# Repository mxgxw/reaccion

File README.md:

Red de Acción Comunitaria (Reaccion.net)
========================================

"Reaccion.net es una Red de Acción Comunitaria que hace uso de un
dispositivo electrónico que facilita la comunicación y coordinación
de comunidades en caso de siniestros, canalizando eficazmente la
información de alerta temprana y necesidades básicas durante
y después de una emergencia..."

El dispositivo consiste en un módulo de transmisión de datos
inalámbrico diseñado específicamente para enviar mensajes
pre-acordados en la forma de mensajes cortos tipo "semáforo"
indicando distintos niveles de alerta o impácto en una comunidad.
Los dispositivos almacenan y actualizan la información entre si al
estilo de una red P2P de tal manera que la información se guarda
de manera distribuida en toda la red.

En este proyecto de GitHub encontrarás las notas de diseño,
diagramas eléctricos, diseños de las tabletas de circuito impreso,
hojas técnicas y el sofware necesario para controlar el kit Reaccion.net.

Puedes apoyar este proyecto haciendo un "Fork" del mismo, agregando
mejoras al diseño y/o funcionamiento e incorporándolas de nuevo a
través de un "pull request".

Ayúdanos a materializar esta idea a través de SocialLab iniciado
sesión con Faceebok y haciendo click a "Vota por esta idea":

http://www.socialab.com/ideas/ver/15704

Para más información contactanos a través de nuestro
email: info _arroba_ reaccion *punto* net.

Últimas adiciones
=================

+Agregadas las hojas técnicas de los componentes bajo extra/Datasheets.

Costo/Lista de Materiales
=========================

Encuentra la lista de materiales en el archivo bom.csv

Pre-requisitos/Requerimientos
=============================

Pendiente diseño del módulo de cargador/regulador de voltaje LiPO.

Construcción y uso
==================

// TO DO

Carpetas
========

```
raíz
 |--dsn: Archivos de diseño
 |   |--main: Esquemáticos y diagrama de PCB para Eagle.
 |   |--auxiliar: Esquemático y diagrama de PCB en formato PDF imprimible.
 |--doc: Archivos de documentación para construcción y uso.
 |--src: Código fuente del software de control (Arduino).
 |--extra: Anexos
     |--Datasheets: Hojas técnicas de los componentes utilizados.
     |--Gráficos: Renders y bocetos del diseño.
     |--sketchs: Esquemas a mano rápidamente.
```

Excepción de responsabilidades
==============================

> El presente proyecto se comparte "tal cual" con el único objetivo de que sea útil.
El/los creadores del presente hardware y su software asociado no pueden garantizar su
correcto funcionamiento bajo ninguna circunstancia. El/Los autor/es de este proyecto
no podrá/n hacerse responsable/s de cualquier pérdida de carácter material, personal o
económico a su persona o terceros derivados de la utilización del mismo. Este diseño
utiliza componentes emisores de radiofrecuencia que podrían requerir algún tipo de
licenciamiento o pruebas de emisiones antes de su puesta en funcionamiento, asegurate
de estar al tanto de las regulaciones locales respecto al tema.

Licenciamiento
==============
El código fuente del software utilizado en este proyecto está protegido bajo la
licencia GNU/GPL v2.0.

Los archivos de diseño principales y auxiliares están liberados bajo la licencia
CC-BY-SA 3.0 ( https://creativecommons.org/licenses/by-sa/3.0/ ).

> La plantilla de este README.md ha sido desarrollada por la comunidad openhardware.sv
con el objetivo de facilitar la documentación de proyectos. Esta plantilla está protegida
bajo la licencia CC BY, puedes modificarla y redistribuirla manteniendo esta nota de
atribución del autor.

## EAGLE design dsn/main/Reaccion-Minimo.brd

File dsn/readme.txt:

Archivos de diseño
==================

Encuentra en esta carpeta los archivos de diagramas eléctricos para el
armado del módulo de tranmisión de datos.

Archivos de diseño principal:

* main\Enlaza.sch : Archivo fuente del diagráma eléctrico para Eagle.
* main\Enlaza.brd : Archivo fuente de la tableta impresa para Eagle.

Archivos de diseño auxiliar:
* auxiliar\Enlaza.pdf : PDF para impresión del diagrama eléctrico.

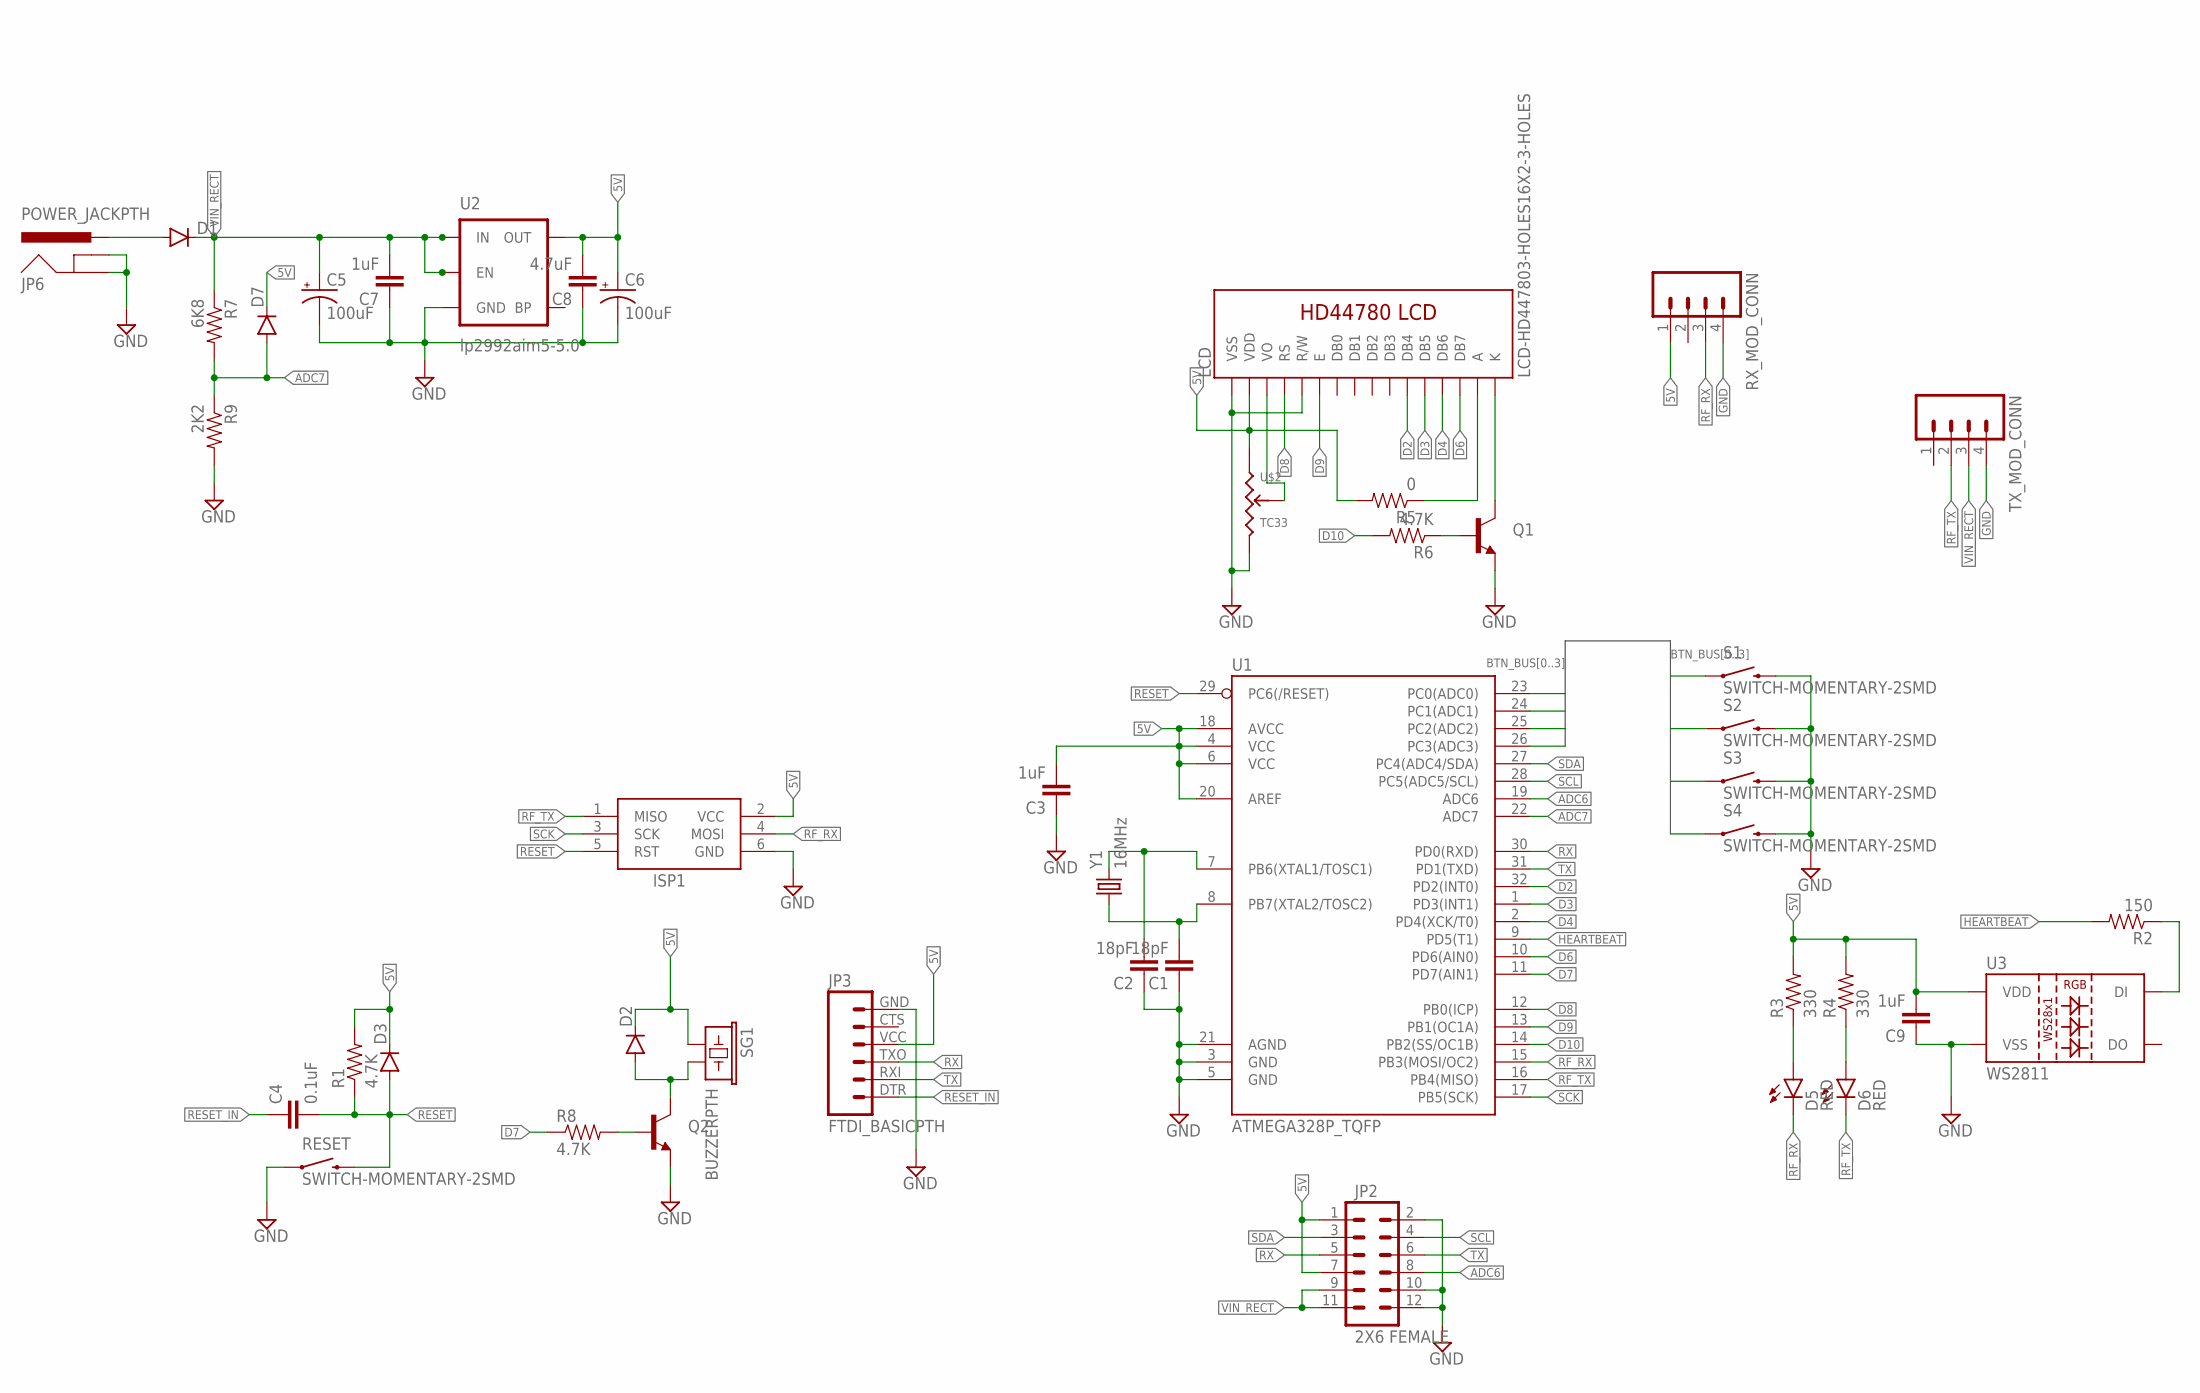
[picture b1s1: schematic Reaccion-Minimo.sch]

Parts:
C1, C2: 18pF; 0805
C3, C7, C9: 1uF; 0805
C4: 0.1uF; 0805
C5: 100uF; C/6032-28R
C6: 100uF; T/3528-12R
C8: 4.7uF; 0805
D1: DIODESMB; SMB-DIODE
D2, D3, D7: DIODESOD123; SOD-123
D5, D6: RED; LED-1206
ISP1: AVRISP-6; AVRISP
JP2: 2X6 FEMALE; 2X6
JP3: FTDI_BASICPTH; FTDI_BASIC
JP6: POWER_JACKPTH; POWER_JACK_PTH
LCD: LCD-HD447803-HOLES16X2-3-HOLES; LCD-16X2-3HOLES
Q1, Q2: TRANSISTOR_NPNSOT23-3; SOT23-3
R1, R6, R8: 4.7K; 0805
R2: 150; 0805
R3, R4: 330; 0805
R5: 0; 0805
R7: 6K8; 0805
R9: 2K2; 0805
RESET: SWITCH-MOMENTARY-2SMD; TACTILE-SWITCH-SMD
RX_MOD_CONN: M04PTH; 1X04
S1, S2, S3, S4: SWITCH-MOMENTARY-2SMD; TACTILE-SWITCH-SMD
SG1: BUZZERPTH; BUZZER-12MM
TX_MOD_CONN: M04PTH; 1X04
U1: ATMEGA328P_TQFP; TQFP32-08
U2: lp2992aim5-5.0; SOT23-5
U3: WS2811; LED-TRICOLOR-5050-IC
U$2: TC33
Y1: 16MHz; CRYSTAL-SMD-5X3

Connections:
5V: C3.2, C6.+, C8.2, C9.2, D2.C, D3.C, D7.C, ISP1.2 (VCC), JP2.1, JP2.7, JP3.VCC (4), LCD.2 (VDD), R1.2, R3.2, R4.2, R5.2, RX_MOD_CONN.1, SG1.+ (1), U1.4 (VCC), U1.6 (VCC), U1.18 (AVCC), U1.20 (AREF), U2.5 (OUT), U3.3 (VDD), U3.5 (VDD), U$2.1
ADC6: JP2.8, U1.19 (ADC6)
ADC7: D7.A, R7.2, R9.1, U1.22 (ADC7)
BTN_BUS0: S1.1, U1.23 (PC0(ADC0))
BTN_BUS1: S2.1, U1.24 (PC1(ADC1))
BTN_BUS2: S3.1, U1.25 (PC2(ADC2))
BTN_BUS3: S4.1, U1.26 (PC3(ADC3))
D2: LCD.11 (DB4), U1.32 (PD2(INT0))
D3: LCD.12 (DB5), U1.1 (PD3(INT1))
D4: LCD.13 (DB6), U1.2 (PD4(XCK/T0))
D6: LCD.14 (DB7), U1.10 (PD6(AIN0))
D7: R8.1, U1.11 (PD7(AIN1))
D8: LCD.4 (RS), U1.12 (PB0(ICP))
D9: LCD.6 (E), U1.13 (PB1(OC1A))
D10: R6.2, U1.14 (PB2(SS/OC1B))
GND: C1.1, C2.1, C3.1, C5.-, C6.-, C7.1, C8.1, C9.1, ISP1.6 (GND), JP2.2, JP2.10, JP2.12, JP3.GND (6), JP6.GND, JP6.GNDBREAK, LCD.1 (VSS), LCD.5 (R/W), Q1.2 (E), Q2.2 (E), R9.2, RESET.1, RX_MOD_CONN.4, S1.3 (2), S2.3 (2), S3.3 (2), S4.3 (2), TX_MOD_CONN.4, U1.3 (GND), U1.5 (GND), U1.21 (AGND), U2.2 (GND), U3.6 (VSS), U$2.3
HEARTBEAT: R2.2, U1.9 (PD5(T1))
unnamed: C2.2, U1.7 (PB6(XTAL1/TOSC1)), Y1.3 (2)
unnamed: C1.2, U1.8 (PB7(XTAL2/TOSC2)), Y1.1
unnamed: R2.1, U3.2 (DI)
unnamed: D5.A, R3.1
unnamed: D6.A, R4.1
unnamed: LCD.15 (A), R5.1
unnamed: LCD.3 (VO), U$2.2
unnamed: LCD.16 (K), Q1.3 (C)
unnamed: Q1.1 (B), R6.1
unnamed: D2.A, Q2.3 (C), SG1.- (2)
unnamed: Q2.1 (B), R8.2
RESET: C4.2, D3.A, ISP1.5 (RST), R1.1, RESET.3 (2), U1.29 (PC6(/RESET))
RESET_IN: C4.1, JP3.DTR (1)
RF_RX: D5.C, ISP1.4 (MOSI), RX_MOD_CONN.3, U1.15 (PB3(MOSI/OC2))
RF_TX: D6.C, ISP1.1 (MISO), TX_MOD_CONN.2, U1.16 (PB4(MISO))
RX: JP2.5, JP3.TXO (3), U1.30 (PD0(RXD))
SCK: ISP1.3 (SCK), U1.17 (PB5(SCK))
SCL: JP2.4, U1.28 (PC5(ADC5/SCL))
SDA: JP2.3, U1.27 (PC4(ADC4/SDA))
TX: JP2.6, JP3.RXI (2), U1.31 (PD1(TXD))
VIN: D1.A, JP6.PWR
VIN_RECT: C5.+, C7.2, D1.C, JP2.9, JP2.11, R7.1, TX_MOD_CONN.3, U2.1 (IN), U2.3 (EN)

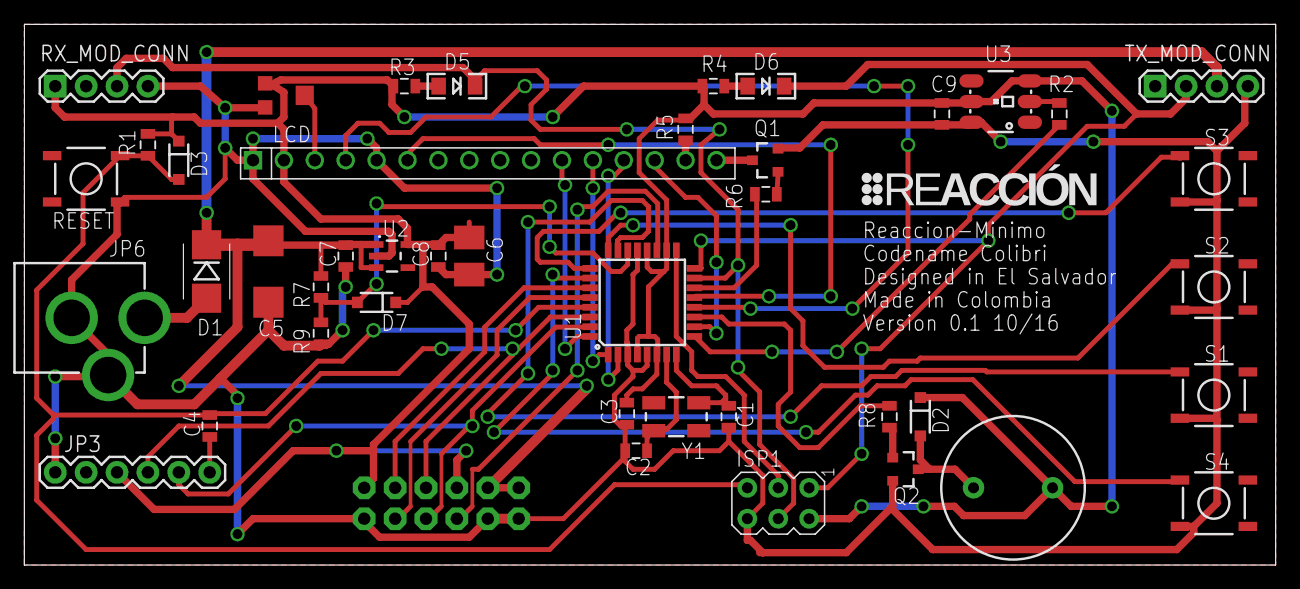
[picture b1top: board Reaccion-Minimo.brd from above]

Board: 2 copper layers, 102.9 x 44.5 mm, 44 parts (1 on the bottom side), 39 nets.

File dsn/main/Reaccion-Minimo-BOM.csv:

"Qty";"Value";"Device";"Package";"Parts";"Description";"PROD_ID";"VALUE";
"1";"";"DIODESMB";"SMB-DIODE";"D1";"Diode";"DIO-09646";"";
"3";"";"DIODESOD123";"SOD-123";"D2, D3, D7";"Diode";"";"";
"2";"";"M04PTH";"1X04";"RX_MOD_CONN, TX_MOD_CONN";"Header 4";"";"";
"2";"";"TRANSISTOR_NPNSOT23-3";"SOT23-3";"Q1, Q2";"Generic NPN BJT";"TRANS-08049";"";
"1";"0";"RESISTOR0805-RES";"0805";"R5";"Resistor";"";"";
"1";"0.1uF";"CAP0805";"0805";"C4";"Capacitor";"";"";
"1";"100uF";"CPOL-USB/3528-21R";"T/3528-12R";"C6";"POLARIZED CAPACITOR, American symbol";"";"";
"1";"100uF";"CPOL-USC/6032-28R";"C/6032-28R";"C5";"POLARIZED CAPACITOR, American symbol";"";"";
"1";"10K";"RESISTOR0805-RES";"0805";"R1";"Resistor";"";"";
"1";"150";"RESISTOR0805-RES";"0805";"R2";"Resistor";"";"";
"1";"16MHz";"CRYSTAL5X3";"CRYSTAL-SMD-5X3";"Y1";"Various standard crystals. Proven footprints.";"XTAL-08218";"";
"2";"18pF";"CAP0805";"0805";"C1, C2";"Capacitor";"";"";
"3";"1uF";"CAP0805";"0805";"C3, C7, C9";"Capacitor";"";"";
"1";"2K2";"RESISTOR0805-RES";"0805";"R9";"Resistor";"";"";
"1";"2X6 FEMALE";"M06X2PTH_FEMALE";"2X6";"JP2";"";"CONN-12423";"2X6 FEMALE";
"2";"330";"RESISTOR0805-RES";"0805";"R3, R4";"Resistor";"";"";
"2";"4.7K";"RESISTOR0805-RES";"0805";"R6, R8";"Resistor";"";"";
"1";"4.7uF";"CAP0805";"0805";"C8";"Capacitor";"";"";
"1";"6K8";"RESISTOR0805-RES";"0805";"R7";"Resistor";"";"";
"1";"ATMEGA328P_TQFP";"ATMEGA328P_TQFP";"TQFP32-08";"U1";"";"IC-09069";"ATMEGA328P_TQFP";
"1";"AVRISP-6";"AVRISP-6";"AVRISP";"ISP1";"AVR ISP HEADER";"";"";
"1";"BUZZERPTH";"BUZZERPTH";"BUZZER-12MM";"SG1";"Buzzer 12mm";"";"";
"1";"FTDI_BASICPTH";"FTDI_BASICPTH";"FTDI_BASIC";"JP3";"FTDI Basic header with labels";"";"";
"1";"LCD-HD447803-HOLES16X2-3-HOLES";"LCD-HD447803-HOLES16X2-3-HOLES";"LCD-16X2-3HOLES";"LCD";"";"";"";
"1";"MIC5219 5V";"V_REG_MIC52195V";"SOT23-5";"U2";"V_REG MIC5219";"VREG-10107";"MIC5219 5V";
"1";"POWER_JACKPTH";"POWER_JACKPTH";"POWER_JACK_PTH";"JP6";"Power Jack";"CONN-08197";"";
"2";"RED";"LED-RED1206";"LED-1206";"D5, D6";"Assorted Red LEDs";"DIO-09912";"RED";
"5";"SWITCH-MOMENTARY-2SMD";"SWITCH-MOMENTARY-2SMD";"TACTILE-SWITCH-SMD";"RESET, S1, S2, S3, S4";"Various NO switches- pushbuttons, reed, etc";"SWCH-08247";"";
"1";"TC33";"TC33";"TC33";"U$2";"";"";"";
"1";"WS2811";"LED-TRICOLOR-5050-ICWS2811";"LED-TRICOLOR-5050-IC";"U3";"WS2812 RGB LED w/ WS2811 driver";"DIO-11598";"WS2811";

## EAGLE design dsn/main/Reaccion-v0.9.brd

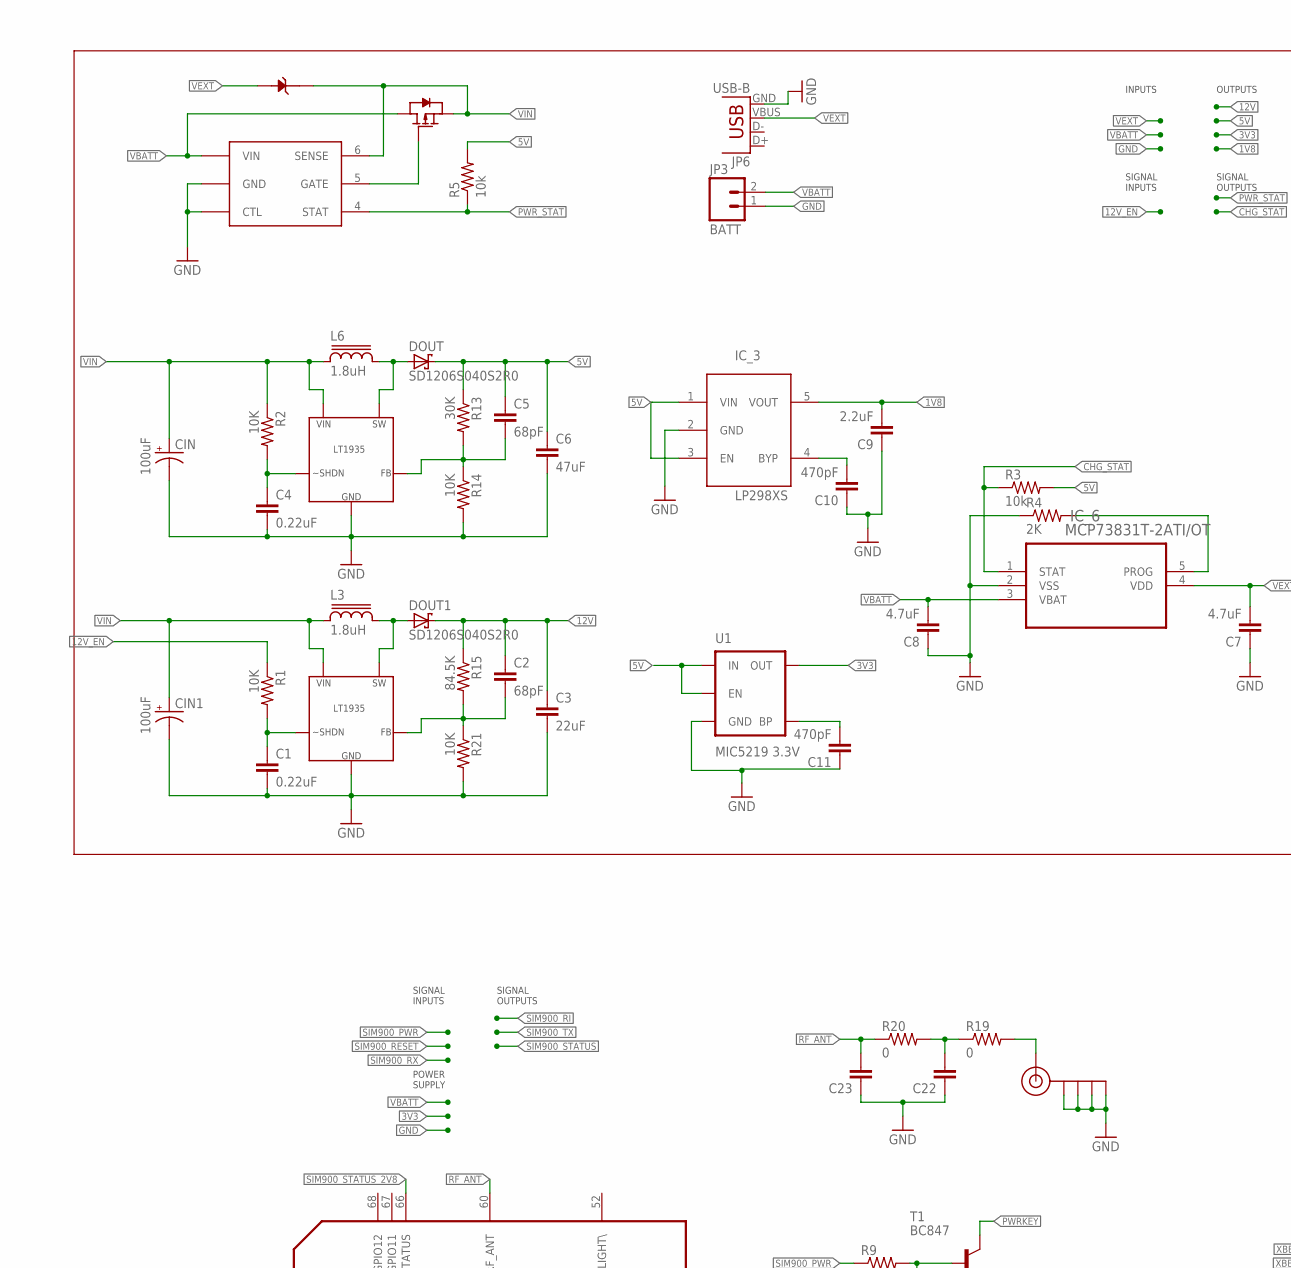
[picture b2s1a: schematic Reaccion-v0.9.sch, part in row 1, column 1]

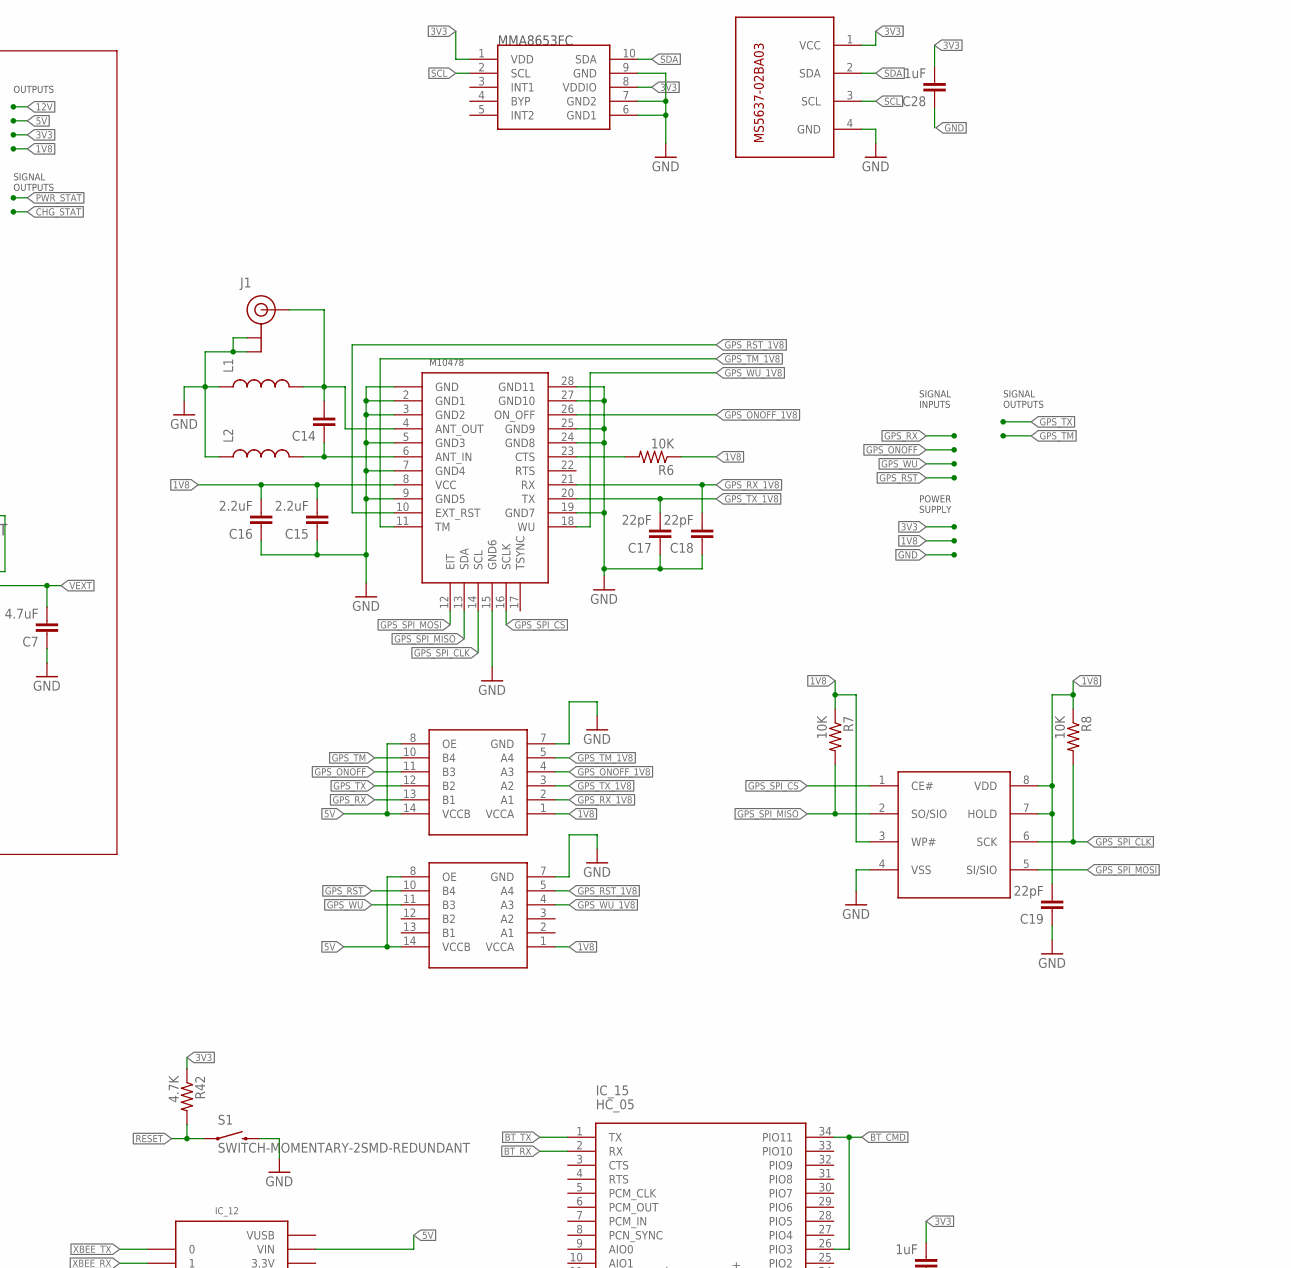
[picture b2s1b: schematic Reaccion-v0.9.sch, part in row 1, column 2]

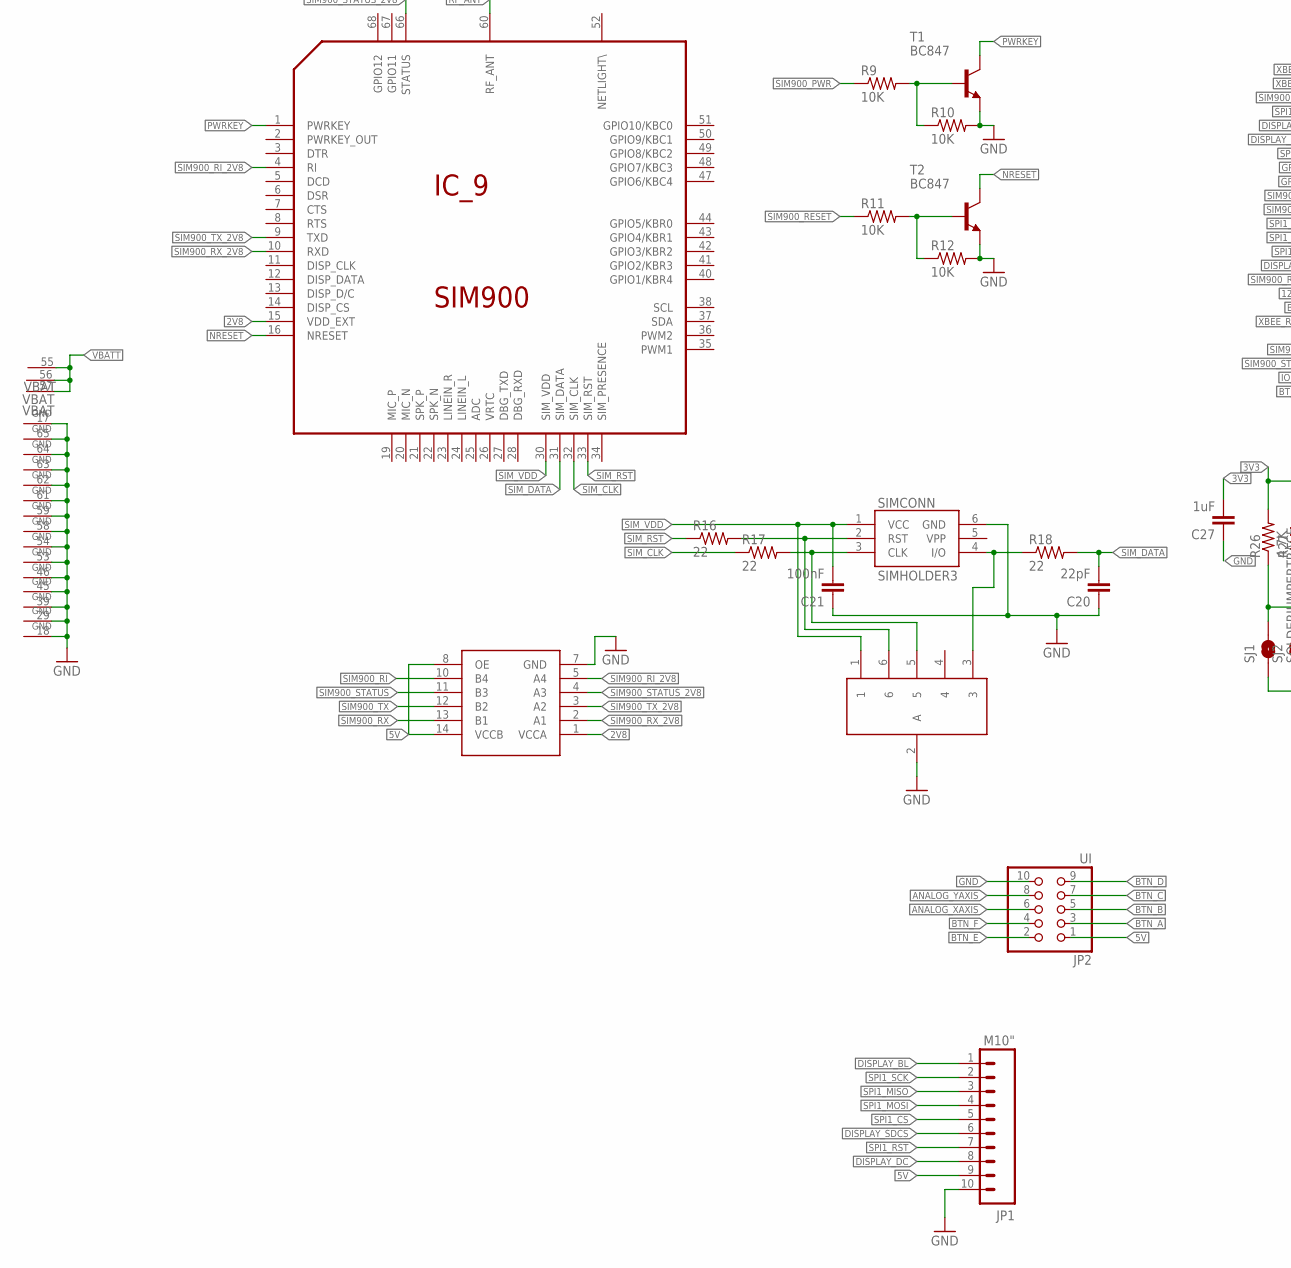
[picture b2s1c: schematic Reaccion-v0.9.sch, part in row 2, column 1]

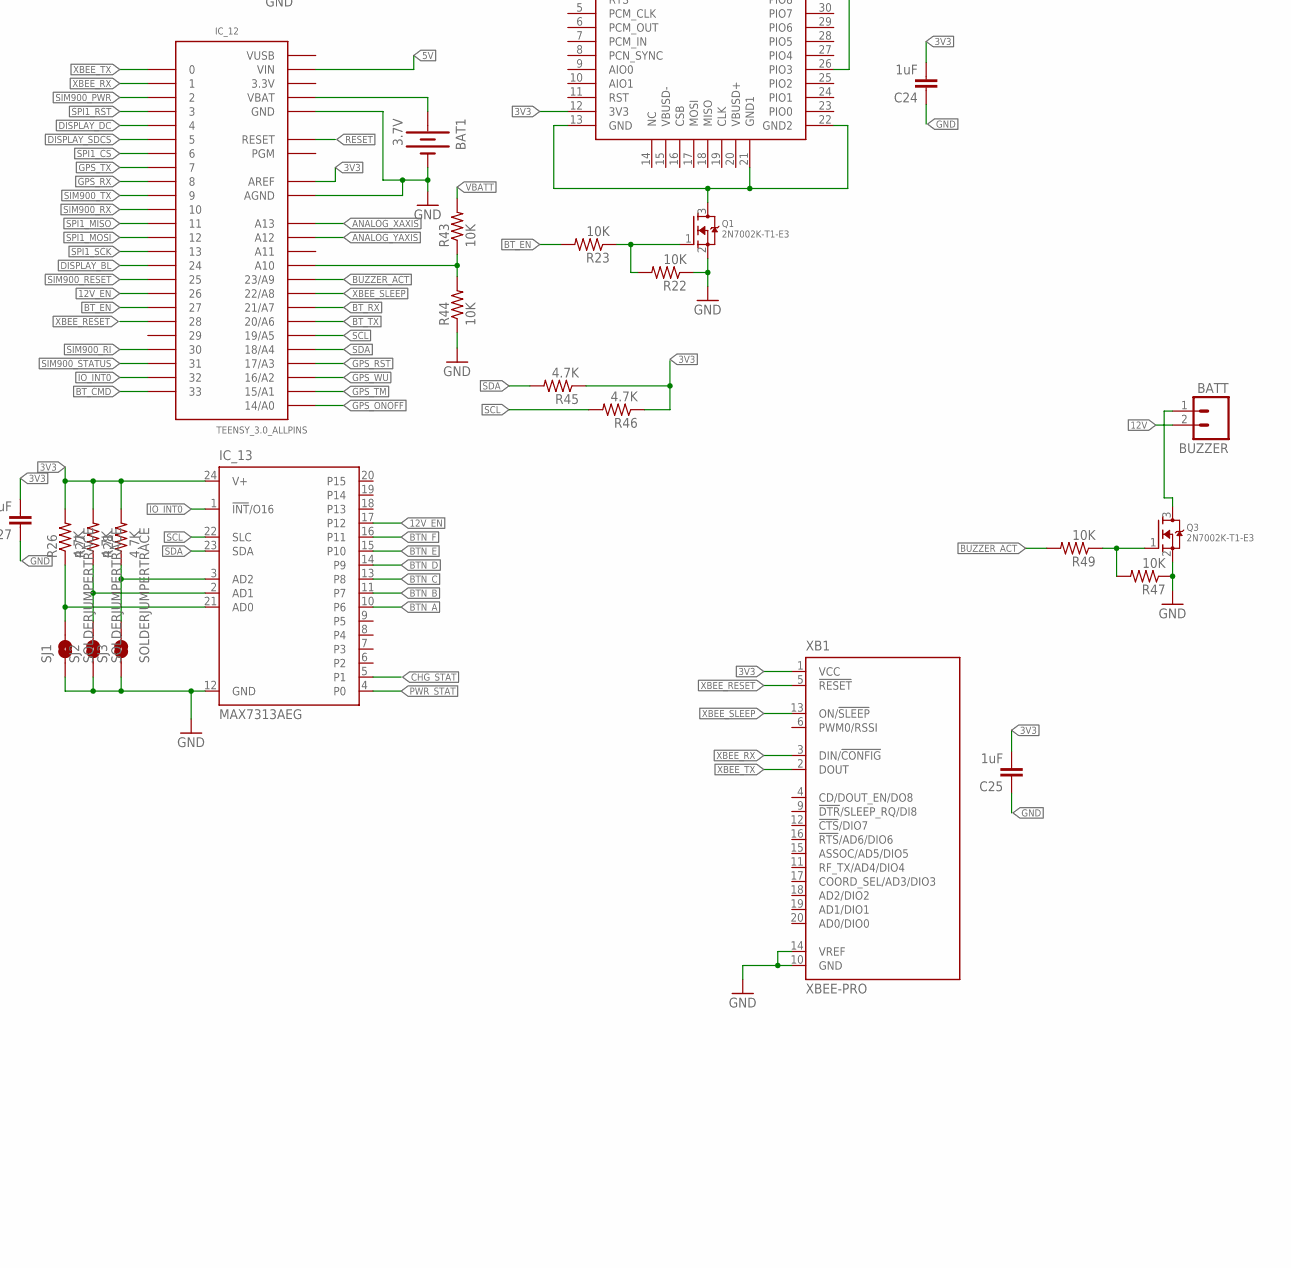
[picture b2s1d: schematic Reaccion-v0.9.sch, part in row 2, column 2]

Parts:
BAT1: 3.7V; BATTCON_12MM
BUZZER: BATT; JST-2-PTH-NS
C1, C4: 0.22uF; 0805
C2, C5: 68pF; 0805
C3: 22uF; 0805
C6: 47uF; 0805
C7, C8: 4.7uF; 0805
C9, C15, C16: 2.2uF; 0805
C10, C11: 470pF; 0805
C14, C22, C23: CAP0805; 0805
C17, C18, C19, C20: 22pF; 0805
C21: 100nF; 0805
C24, C25, C27, C28: 1uF; 0805
CIN, CIN1: 100uF; 1210-POLARIZED
D4: 1N5819HW-7-F; SOD123
DOUT, DOUT1: SD1206S040S2R0; 1206-POL
IC_1: LTC4412; SOT23-6L
IC_3: LP298XS; SOT23-5L
IC_6: MCP73831T-2ATI/OT; SOT95P300X145-5N
IC_7: MMA8653FC; 2X2-DFN
IC_8: MS5637-02BA03
IC_9: SIM900
IC_10, IC_17, IC_18: TXB0104; SO14
IC_11: SMF05C; SOT665
IC_12: TEENSY_3.0_ALLPINS
IC_13: MAX7313AEG; QSOP24
IC_15: HC_05; BLUETOOTH_SMD
IC_16: M10478
IC_19: SST25WF040B; SO08
J1: U.FL
J$1: SMA_EDGE; SMA-EDGE
JP1: M10"; 1X10
JP2: UI; 2X05
JP3: BATT; JST-2-PTH-NS
JP6: USB-B; USB-B-PTH
L1, L2: INDUCTOR0805; 0805
L3, L6: 1.8uH; SRR4028
Q1, Q3: 2N7002K-T1-E3; SOT23
Q9: SI2301CDS; SOT23
R1, R2, R6, R7, R8, R9, R10, R11, R12, R14, R21, R22, R23, R43, R44, R47, R49: 10K; 0805
R3, R5: 10k; 0805
R4: 2K; 0805
R13: 30K; 0805
R15: 84.5K; 0805
R16, R17, R18: 22; 0805
R19, R20: 0; 0805
R26, R27, R28, R42, R45, R46: 4.7K; 0805
S1: SWITCH-MOMENTARY-2SMD-REDUNDANT; TACTILE-SWITCH-SMD
SIMCONN: SIMHOLDER3
SJ1, SJ2, SJ3: SOLDERJUMPERTRACE; SJ_2S-TRACE
T1, T2: BC847; SOT23
U1: MIC5219 3.3V; SOT23-5
U$1, U$2: LT1935ES5; SOT23-5
XB1: XBEE-PRO

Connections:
1V8: C9.2, C15.2, C16.2, C19.2, IC_3.5 (VOUT), IC_16.8 (VCC), IC_17.1 (VCCA), IC_18.1 (VCCA), IC_19.3 (WP#), IC_19.7 (HOLD), IC_19.8 (VDD), R6.1, R7.1, R8.1
2V8: IC_9.15 (VDD_EXT), IC_10.1 (VCCA)
3.3V: IC_12.3.3V, IC_12.3.3V1 (3.3V), IC_12.3.3V2 (3.3V)
3V3: C24.2, C25.2, C27.2, C28.2, IC_7.1 (VDD), IC_7.8 (VDDIO), IC_8.1 (VCC), IC_12.AREF, IC_13.24 (V+), IC_15.12 (3V3), R26.2, R27.2, R28.2, R42.1, R45.1, R46.1, U1.5 (OUT), XB1.1 (VCC)
5V: C5.1, C6.1, DOUT.2 (C), IC_3.1 (VIN), IC_3.3 (EN), IC_10.8 (OE), IC_10.14 (VCCB), IC_12.VIN, IC_17.8 (OE), IC_17.14 (VCCB), IC_18.8 (OE), IC_18.14 (VCCB), JP1.9, JP2.1, R3.2, R5.2, R13.1, U1.1 (IN), U1.3 (EN)
12V: BUZZER.2, C2.1, C3.1, DOUT1.2 (C), R15.1
12V_EN: IC_12.26, IC_13.17 (P12), R1.1
ANALOG_XAXIS: IC_12.A13, JP2.6
ANALOG_YAXIS: IC_12.A12, JP2.8
BTN_A: IC_13.10 (P6), JP2.3
BTN_B: IC_13.11 (P7), JP2.5
BTN_C: IC_13.13 (P8), JP2.7
BTN_D: IC_13.14 (P9), JP2.9
BTN_E: IC_13.15 (P10), JP2.2
BTN_F: IC_13.16 (P11), JP2.4
BT_CMD: IC_12.33, IC_15.26 (PIO3), IC_15.34 (PIO11)
BT_EN: IC_12.27, R23.2
BT_RX: IC_12.21/A7, IC_15.2 (RX)
BT_TX: IC_12.20/A6, IC_15.1 (TX)
BUZZER_ACT: IC_12.23/A9, R49.2
CHG_STAT: IC_6.1 (STAT), IC_13.5 (P1), R3.1
DISPLAY_BL: IC_12.24, JP1.1
DISPLAY_DC: IC_12.4, JP1.8
DISPLAY_SDCS: IC_12.5, JP1.6
GND: BAT1.GND (-), C1.2, C3.2, C4.2, C6.2, C7.1, C8.1, C9.1, C10.1, C11.1, C15.1, C16.1, C17.1, C18.1, C19.1, C20.1, C21.1, C22.1, C23.1, C24.1, C25.1, C27.1, C28.1, CIN.2 (-), CIN1.2 (-), IC_1.2 (GND), IC_1.3 (CTL), IC_3.2 (GND), IC_6.2 (VSS), IC_7.6 (GND1), IC_7.7 (GND2), IC_7.9 (GND), IC_8.4 (GND), IC_9.17 (GND), IC_9.18 (GND), IC_9.29 (GND), IC_9.39 (GND), IC_9.45 (GND), IC_9.46 (GND), IC_9.53 (GND), IC_9.54 (GND), IC_9.58 (GND), IC_9.59 (GND), IC_9.61 (GND), IC_9.62 (GND), IC_9.63 (GND), IC_9.64 (GND), IC_9.65 (GND), IC_10.7 (GND), IC_11.2 (A), IC_12.AGND, IC_12.GND, IC_12.GND1 (GND), IC_12.GND2 (GND), IC_13.12 (GND), IC_16.1 (GND), IC_16.2 (GND1), IC_16.3 (GND2), IC_16.5 (GND3), IC_16.7 (GND4), IC_16.9 (GND5), IC_16.15 (GND6), IC_16.19 (GND7), IC_16.24 (GND8), IC_16.25 (GND9), IC_16.27 (GND10), IC_16.28 (GND11), IC_17.7 (GND), IC_18.7 (GND), IC_19.4 (VSS), J1.P$1 (GND), J1.P$2 (GND), J$1.GND@0 (GND), J$1.GND@1 (GND), J$1.GND@2 (GND), J$1.GND@3 (GND), JP1.10, JP2.10, JP3.1, JP6.GND, L1.1, L2.1, Q1.2 (S), Q3.2 (S), R4.1, R10.2, R12.2, R14.2, R21.2, R22.1, R44.1, R47.1, S1.3 (2), S1.4 (2), SIMCONN.6 (GND), SJ1.1, SJ2.1, SJ3.1, T1.2 (E), T2.2 (E), U1.2 (GND), U$1.2 (GND), U$2.2 (GND), XB1.10 (GND), XB1.14 (VREF)
GPS_ONOFF: IC_12.14/A0, IC_17.11 (B3)
GPS_ONOFF_1V8: IC_16.26 (ON_OFF), IC_17.4 (A3)
GPS_RST: IC_12.17/A3, IC_18.10 (B4)
GPS_RST_1V8: IC_16.10 (EXT_RST), IC_18.5 (A4)
GPS_RX: IC_12.8, IC_17.13 (B1)
GPS_RX_1V8: C18.2, IC_16.21 (RX), IC_17.2 (A1)
GPS_SPI_CLK: IC_16.14 (SCL), IC_19.6 (SCK), R8.2
GPS_SPI_CS: IC_16.16 (SCLK), IC_19.1 (CE#)
GPS_SPI_MISO: IC_16.13 (SDA), IC_19.2 (SO/SIO), R7.2
GPS_SPI_MOSI: IC_16.12 (EIT), IC_19.5 (SI/SIO)
GPS_TM: IC_12.15/A1, IC_17.10 (B4)
GPS_TM_1V8: IC_16.11 (TM), IC_17.5 (A4)
GPS_TX: IC_12.7, IC_17.12 (B2)
GPS_TX_1V8: C17.2, IC_16.20 (TX), IC_17.3 (A2)
GPS_WU: IC_12.16/A2, IC_18.11 (B3)
GPS_WU_1V8: IC_16.18 (WU), IC_18.4 (A3)
IO_INT0: IC_12.32, IC_13.1 (!INT!/O16)
unnamed: DOUT1.1 (A), L3.2, U$2.1 (SW)
unnamed: DOUT.1 (A), L6.2, U$1.1 (SW)
unnamed: C1.1, R1.2, U$2.4 (SHDN)
unnamed: C11.2, U1.4 (BP)
unnamed: C2.2, R15.2, R21.1, U$2.3 (FB)
unnamed: C5.2, R13.2, R14.1, U$1.3 (FB)
unnamed: C4.1, R2.2, U$1.4 (SHDN)
unnamed: IC_6.5 (PROG), R4.2
unnamed: IC_1.5 (GATE), Q9.1 (GATE)
unnamed: C10.2, IC_3.4 (BYP)
unnamed: C14.1, IC_16.6 (ANT_IN), L2.2
unnamed: C14.2, IC_16.4 (ANT_OUT), J1.P$3 (SIGNAL), L1.2
unnamed: BUZZER.1, Q3.3 (D)
unnamed: IC_16.23 (CTS), R6.2
unnamed: R9.2, R10.1, T1.1 (B)
unnamed: R11.2, R12.1, T2.1 (B)
unnamed: IC_15.13 (GND), IC_15.21 (GND1), IC_15.22 (GND2), Q1.3 (D)
unnamed: IC_11.3, R18.1, SIMCONN.4 (I/O)
unnamed: C22.2, R19.1, R20.2
unnamed: IC_11.6, R16.2, SIMCONN.2 (RST)
unnamed: IC_11.5, R17.2, SIMCONN.3 (CLK)
unnamed: J$1.SIG (SIGNAL), R19.2
unnamed: Q1.1 (G), R22.2, R23.1
unnamed: Q3.1 (G), R47.2, R49.1
unnamed: IC_13.21 (AD0), R26.1, SJ1.2
unnamed: IC_13.3 (AD2), R28.1, SJ3.2
unnamed: IC_13.2 (AD1), R27.1, SJ2.2
unnamed: BAT1.PWR@1 (+), IC_12.VBAT
unnamed: IC_12.A10, R43.1, R44.2
NRESET: IC_9.16 (NRESET), T2.3 (C)
PWRKEY: IC_9.1 (PWRKEY), T1.3 (C)
PWR_STAT: IC_1.4 (STAT), IC_13.4 (P0), R5.1
RESET: IC_12.RESET, R42.2, S1.1, S1.2 (1)
RF_ANT: C23.2, IC_9.60 (RF_ANT), R20.1
SCL: IC_7.2 (SCL), IC_8.3 (SCL), IC_12.19/A5, IC_13.22 (SLC), R46.2
SDA: IC_7.10 (SDA), IC_8.2 (SDA), IC_12.18/A4, IC_13.23 (SDA), R45.2
SIM900_PWR: IC_12.2, R9.1
SIM900_RESET: IC_12.25, R11.1
SIM900_RI: IC_10.10 (B4), IC_12.30
SIM900_RI_2V8: IC_9.4 (RI), IC_10.5 (A4)
SIM900_RX: IC_10.13 (B1), IC_12.10
SIM900_RX_2V8: IC_9.10 (RXD), IC_10.2 (A1)
SIM900_STATUS: IC_10.11 (B3), IC_12.31
SIM900_STATUS_2V8: IC_9.66 (STATUS), IC_10.4 (A3)
SIM900_TX: IC_10.12 (B2), IC_12.9
SIM900_TX_2V8: IC_9.9 (TXD), IC_10.3 (A2)
SIM_CLK: IC_9.32 (SIM_CLK), R17.1
SIM_DATA: C20.2, IC_9.31 (SIM_DATA), R18.2
SIM_RST: IC_9.33 (SIM_RST), R16.1
SIM_VDD: C21.2, IC_9.30 (SIM_VDD), IC_11.1, SIMCONN.1 (VCC)
SPI1_CS: IC_12.6, JP1.5
SPI1_MISO: IC_12.11, JP1.3
SPI1_MOSI: IC_12.12, JP1.4
SPI1_RST: IC_12.3, JP1.7
SPI1_SCK: IC_12.13, JP1.2
VBATT: C8.2, IC_1.1 (VIN), IC_6.3 (VBAT), IC_9.55 (VBAT), IC_9.56 (VBAT), IC_9.57 (VBAT), JP3.2, Q9.3 (DRAIN), R43.2
VEXT: C7.2, D4.2 (ANODE), IC_6.4 (VDD), JP6.VBUS
VIN: CIN.1 (+), CIN1.1 (+), D4.1 (CATHODE), IC_1.6 (SENSE), L3.1, L6.1, Q9.2 (SOURCE), R2.1, U$1.5 (VIN), U$2.5 (VIN)
VUSB: IC_12.VUSB
XBEE_RESET: IC_12.28, XB1.5 (!RESET)
XBEE_RX: IC_12.1, XB1.3 (DIN/!CONFIG)
XBEE_SLEEP: IC_12.22/A8, XB1.13 (ON/!SLEEP)
XBEE_TX: IC_12.0, XB1.2 (DOUT)

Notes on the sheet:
INPUTS
OUTPUTS
SIGNAL INPUTS
SIGNAL OUTPUTS
POWER SUPPLY

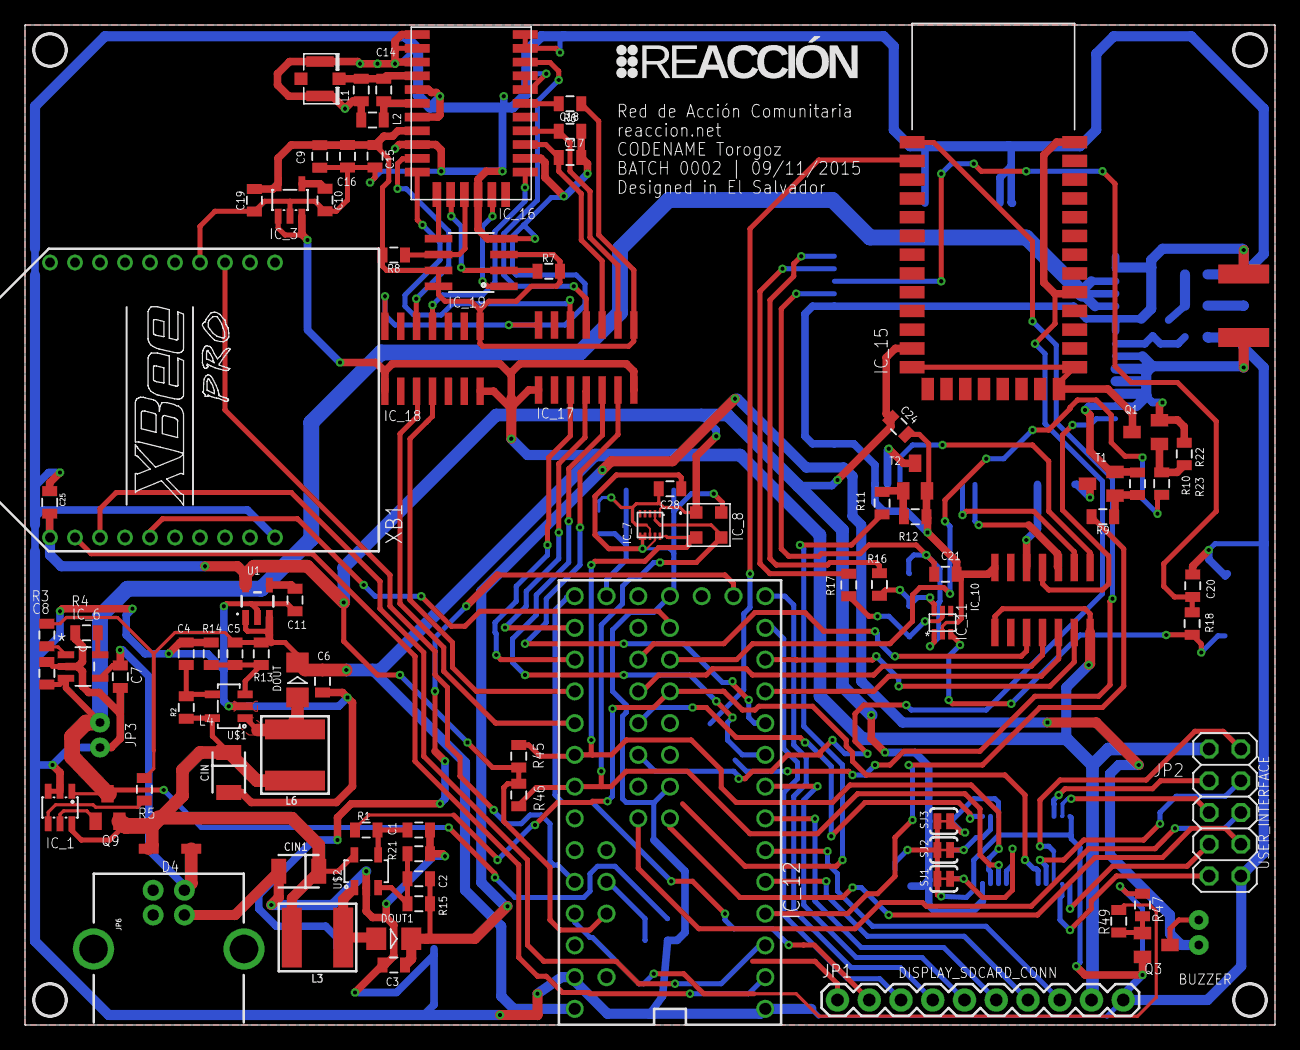
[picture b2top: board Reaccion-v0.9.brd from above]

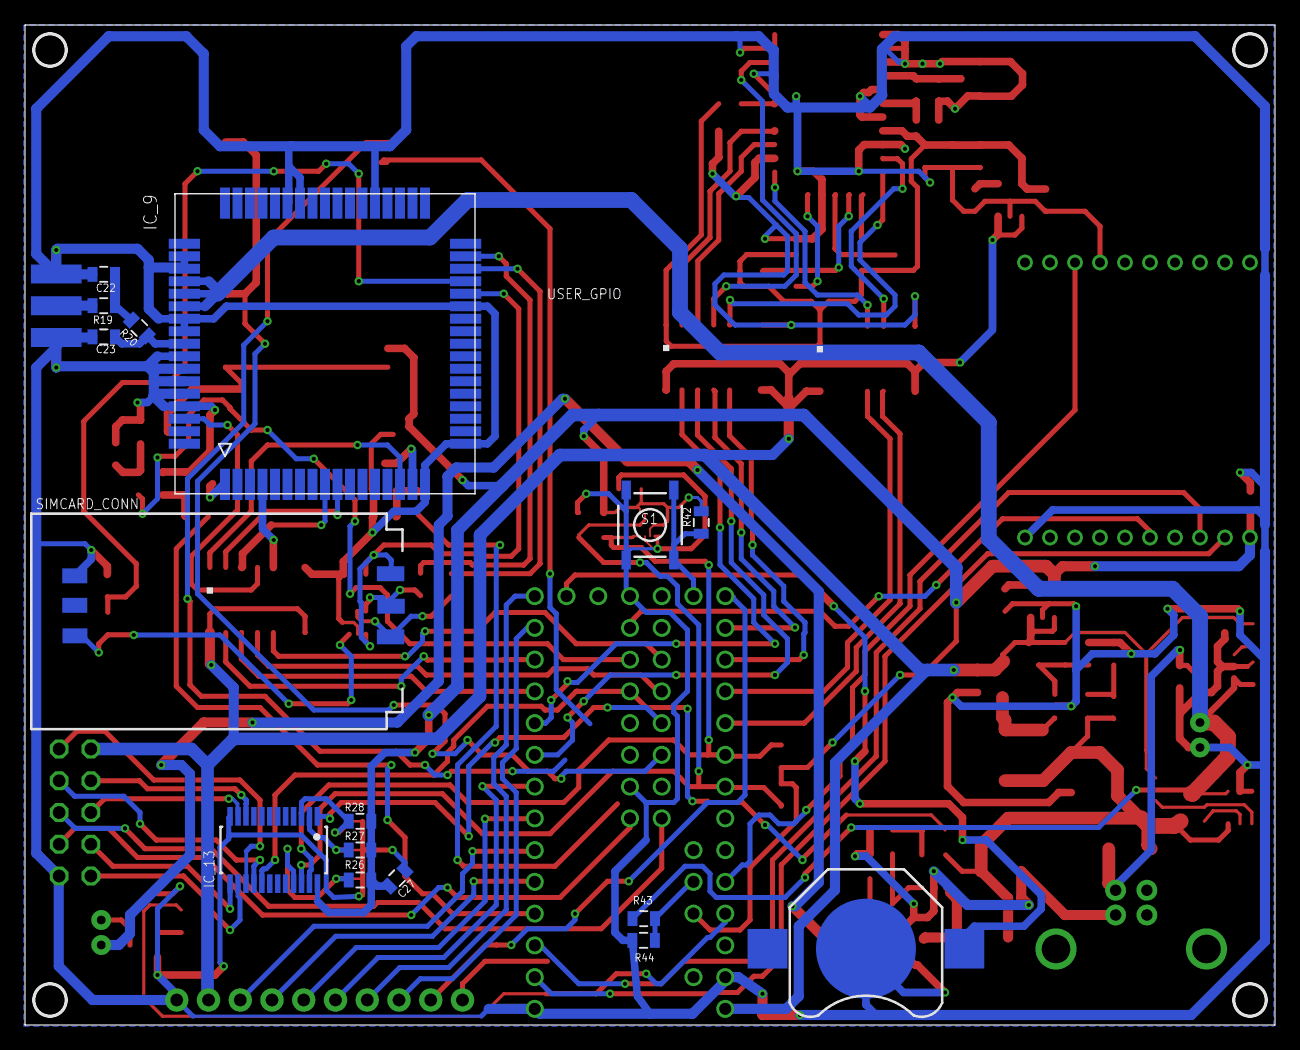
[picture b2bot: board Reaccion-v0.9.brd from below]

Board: 2 copper layers, 100.0 x 80.0 mm, 104 parts (17 on the bottom side), 104 nets.

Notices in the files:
src/ReaccionMinimo/ReaccionMinimo.ino:
Copyright (C) 2016  Mario Gomez/mxgxw < mario.gomez _at- teubi.co >
modify it under the terms of the GNU General Public License
parts and their libraries:
SparkFun-Connectors: Licensing: Creative Commons ShareAlike 4.0 International - https://creativecommons.org/licenses/by-sa/4.0
SparkFun-Capacitors: Licensing: CC v3.0 Share-Alike You are welcome to use this library for commercial purposes.
inductor-bourns: Copyright (C) 2008, Bob Starr
